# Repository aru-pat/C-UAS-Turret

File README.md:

# C-UAS-Turret

A pan-tilt turret that detects and tracks a drone with a self-trained neural
network and fires a low-power laser lock-on indicator. Semester 1: ground-based
turret detecting and tracking drones; semester 2: mount the system on a drone
platform.

Docs (in `docs/`):
- `project-reqs.md` — what the project must do, hardware split, budget
- `prototype-reqs.md` — checklists for Prototypes 1, 2 and 3
- `gantt.md` — timeline by availability window and key dates
- `design-decisions.md` — every design decision and why I made it
- `s42c-bringup-tests.md` — bench test results and the pin/voltage table for the PCB
- `turret_bom.xlsx` — parts list with links, prices, and decide-by / order-by dates

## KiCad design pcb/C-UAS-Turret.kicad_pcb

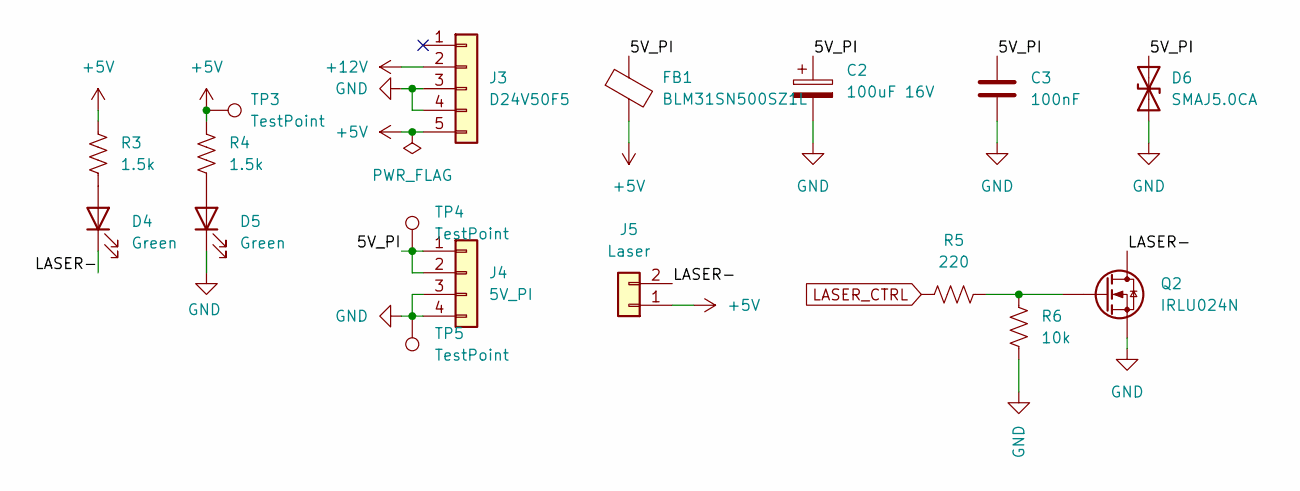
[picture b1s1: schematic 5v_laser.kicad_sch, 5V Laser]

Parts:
C2: 100uF 16V; CP_Radial_D5.0mm_P2.00mm
C3: 100nF; C_0805_2012Metric
D4, D5: Green; LED_0805_2012Metric
D6: SMAJ5.0CA; D_SMA
FB1: BLM31SN500SZ1L; L_1206_3216Metric
J3: D24V50F5; PinHeader_1x05_P2.54mm_Vertical
J4: 5V_PI; JST_XH_B4B-XH-A_1x04_P2.50mm_Vertical
J5: Laser; JST_XH_B2B-XH-A_1x02_P2.50mm_Vertical
Q2: IRLU024N
R3, R4: 1.5k; R_0805_2012Metric
R5: 220; R_0805_2012Metric
R6: 10k; R_0805_2012Metric
TP3, TP4, TP5: TestPoint; TestPoint_THTPad_D2.0mm_Drill1.0mm

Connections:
+5V: FB1.2, J3.5, J5.1, R3.1, R4.1, TP3.1 (1_1)
+12V: J3.2; also elsewhere on the board
/5V and Laser/5V_PI: C2.1, C3.1, D6.2 (A2), FB1.1, J4.1, J4.2, TP4.1 (1_1)
/5V and Laser/LASER-: D4.1 (K), J5.2, Q2.D
GND: C2.2, C3.2, D5.1 (K), D6.1 (A1), J3.3, J3.4, J4.3, J4.4, Q2.S, R6.2, TP5.1 (1_1); also elsewhere on the board
LASER_CTRL: R5.1; also elsewhere on the board
unnamed: D4.2 (A), R3.2
unnamed: D5.2 (A), R4.2
unnamed: Q2.G, R5.2, R6.1

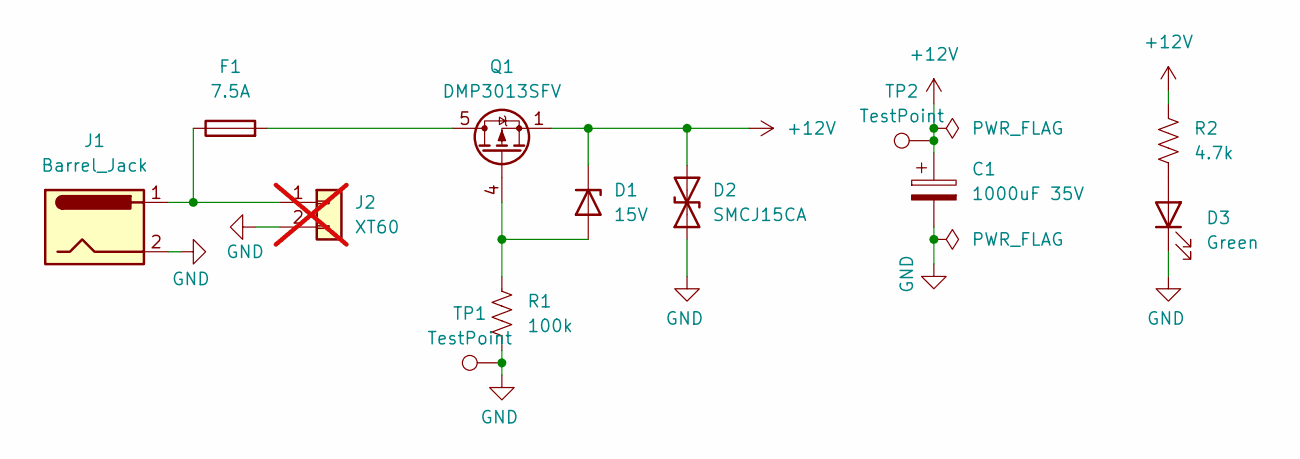
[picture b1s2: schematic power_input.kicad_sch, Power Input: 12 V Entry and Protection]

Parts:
C1: 1000uF 35V; CP_Radial_D12.5mm_P5.00mm
D1: 15V; D_SOD-123
D2: SMCJ15CA; D_SMC
D3: Green; LED_0805_2012Metric
F1: 7.5A; FuseHolder_Blade_ATO_Littelfuse_FLR_178.6165
J1: Barrel_Jack; BarrelJack_CUI_PJ-063AH_Horizontal
J2: XT60; AMASS_XT60PW-M_1x02_P7.20mm_Horizontal; not fitted
Q1: DMP3013SFV; Diodes_PowerDI3333-8
R1: 100k; R_0805_2012Metric
R2: 4.7k; R_0805_2012Metric
TP1, TP2: TestPoint; TestPoint_THTPad_D2.0mm_Drill1.0mm

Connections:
+12V: C1.1, D1.1 (K), D2.2 (A2), Q1.1 (S), Q1.2 (S), Q1.3 (S), R2.1, TP2.1 (1_1); also elsewhere on the board
GND: C1.2, D2.1 (A1), D3.1 (K), J1.2, J2.2, R1.2, TP1.1 (1_1); also elsewhere on the board
unnamed: D1.2 (A), Q1.4 (G), R1.1
unnamed: D3.2 (A), R2.2
unnamed: F1.1, J1.1, J2.1
unnamed: F1.2, Q1.5 (D)

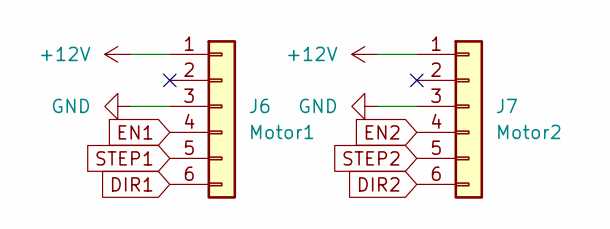
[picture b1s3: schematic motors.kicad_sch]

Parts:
J6: Motor1; JST_XH_B6B-XH-A_1x06_P2.50mm_Vertical
J7: Motor2; JST_XH_B6B-XH-A_1x06_P2.50mm_Vertical

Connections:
+12V: J6.1, J7.1; also elsewhere on the board
DIR1: J6.6; also elsewhere on the board
DIR2: J7.6; also elsewhere on the board
EN1: J6.4; also elsewhere on the board
EN2: J7.4; also elsewhere on the board
GND: J6.3, J7.3; also elsewhere on the board
STEP1: J6.5; also elsewhere on the board
STEP2: J7.5; also elsewhere on the board

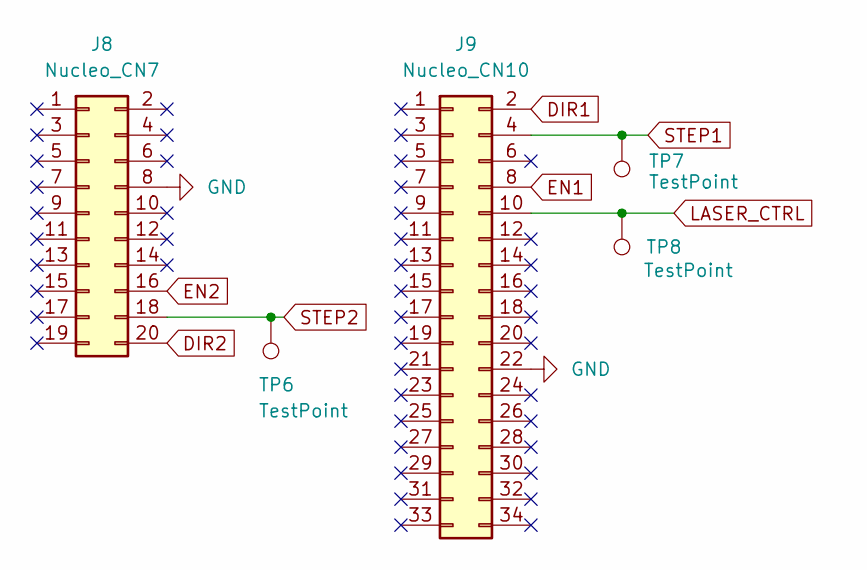
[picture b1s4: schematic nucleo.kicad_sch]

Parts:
J8: Nucleo_CN7; PPPC102LFBN-RC_NucleoZio_2x10
J9: Nucleo_CN10; PPPC172LFBN-RC_NucleoZio_2x17
TP6, TP7, TP8: TestPoint; TestPoint_THTPad_D2.0mm_Drill1.0mm

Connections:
DIR1: J9.2; also elsewhere on the board
DIR2: J8.20; also elsewhere on the board
EN1: J9.8; also elsewhere on the board
EN2: J8.16; also elsewhere on the board
GND: J8.8, J9.22; also elsewhere on the board
LASER_CTRL: J9.10, TP8.1 (1_1); also elsewhere on the board
STEP1: J9.4, TP7.1 (1_1); also elsewhere on the board
STEP2: J8.18, TP6.1 (1_1); also elsewhere on the board

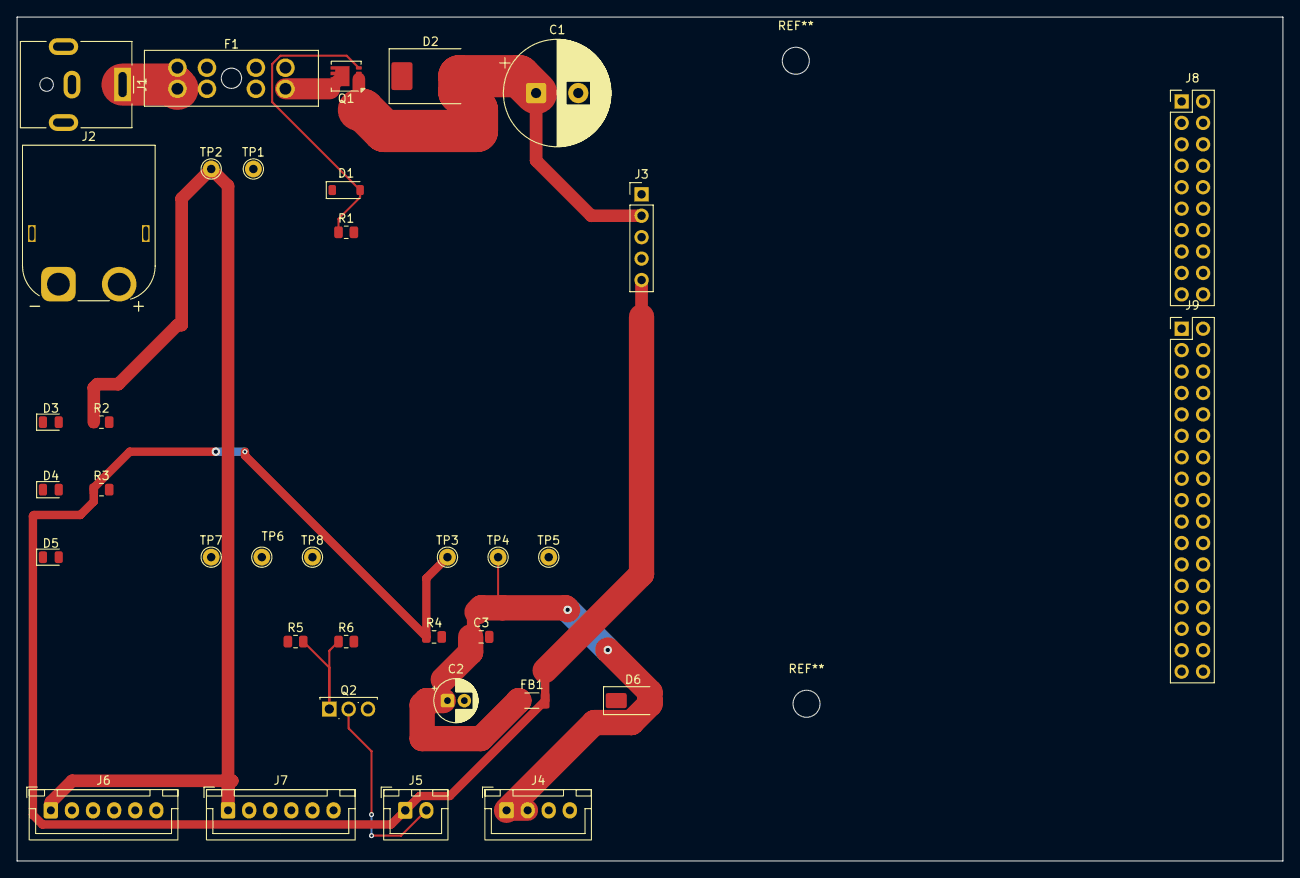
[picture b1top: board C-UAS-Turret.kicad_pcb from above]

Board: 2 copper layers, 150.0 x 100.0 mm, 36 parts (0 on the bottom side), 19 nets.
